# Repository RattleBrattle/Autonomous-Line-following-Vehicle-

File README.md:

## Autonomous Line Following Robot Vehicle

This project implements an autonomous line-following robot using an ATmega32A microcontroller. The robot is capable of detecting and following a line on the ground using TCRT5000 infrared sensors. It can move forward, turn left or right, and reverse based on the sensor inputs. Additionally, the robot is equipped with an HC-SR04 ultrasonic sensor for obstacle detection and an SG-90 servo motor to adjust the sensor's position for better obstacle avoidance.

### Features

- **Line Following**: Uses TCRT5000 infrared sensors to detect and follow a line.
- **Obstacle Detection**: Equipped with an HC-SR04 ultrasonic sensor to detect obstacles and avoid collisions.
- **Servo Motor Control**: Utilizes an SG-90 servo motor to adjust the position of the ultrasonic sensor for a broader range of detection.
- **Motor Control**: Controls DC motors using 2x L293D motor driver ICs for precise movement and direction control.
- **LCD Display**: Displays sensor readings, current direction, and status information (errors) on an LCD screen.

#### Project Flowchart
.png?raw=true)

- A higher detailed Flowchart PDF and image can be found in the "Project flow charts" file uploaded in the repository.

### Hardware Components

- ATmega32A Microcontroller
- TCRT5000 Infrared Sensors (3 units: left, center, right)
- HC-SR04 Ultrasonic Sensor
- SG-90 Servo Motor
- L293D Motor Driver ICs (2 units)
- DC Motors (4 units)
- LCD Display (16x2)
- Resistors, Capacitors, and other passive components

### Software Components

- **MCAL (Microcontroller Abstraction Layer)**
  - DIO (General Purpose Input/Output)
  - Timer (Timer0, Timer1)
  - ADC (Analog to Digital Converter)
  - USART (Universal Synchronous/Asynchronous Receiver/Transmitter)
  - Global Interrupt Enable (GIE)
  
- **HAL (Hardware Abstraction Layer)**
  - TCRT5000 Sensor Driver
  - HC-SR04 Ultrasonic Sensor Driver
  - SG-90 Servo Motor Driver
  - LCD Display Driver
 
### Proteus simulation circuit

  - **Simulation circuit**: In the folder uploaded to the repository named "Line-following robot", where I've created a circuit
  to simulate what the project would look like in real life as close as possible using libraries provided by syedzainnasir over [at this link!](https://www.theengineeringprojects.com/2021/05/infrared-tracker-sensor-library-for-proteus.html)

  - A higher quality image can be found inside the same folder mentioned above.

### Functionality

1. **Initialization**: 
   - Initializes GPIO pins, ADC, Timers, USART, and sensors.
   - Sets up the servo motor and ultrasonic sensor for obstacle detection.
   - Microcontroller controls the Motors and has 3 functions for them:
     1) Steer vehicle right by turning on the 2 right motors.
     2) Steer vehicle left by turning on the 2 left motors.
     3) Move vehicle forward by turning on all motors.
     4) Reverse vehicle backwards by reversing signals on all motors (not used in the project but the function is there and working).

2. **Line Following**:
   - Continuously reads the analog and digital values from the TCRT5000 sensors.
   - Adjusts the motor speeds and directions to follow the detected line.
   - Microcontroller constantly reads analog and digital values from the 3 TCRT sensors:
     1) If the left sensor digital value is 1 and the right sensor digital value is zero, then the vehicle turns left.
     2) If the right sensor digital value is 1 and the left sensor digital value is zero, then the vehicle turns right.
     3) If the middle sensor digital value is 0, the vehicle moves forward.

3. **Obstacle Detection and Avoidance**:
   - Uses the HC-SR04 sensor to measure distances to obstacles.
   - Adjusts the servo motor to scan the area.
   - When an obstacle is detected in range (<20CM), the MCU writes to LCD screen a warning and a Buzzer alarm sounds off.

4. **LCD Display**:
   - Displays the sensor readings and robot status on the LCD screen for monitoring. !!!(For debugging only)!!!
   - Displays current direction the vehicle is going, Obstacles detected when ultrasonic distance is <20CM, and errors when they occur. 

### Usage

1. **Hardware Setup**:
   - Connect the TCRT5000 sensors, HC-SR04 sensor, SG-90 servo motor, L293D motor driver ICs, and DC motors to the ATmega32A microcontroller as per the circuit diagram.

- A higher quality Schematic can be found inside the "PDF files" in the "KiCAD" schematic folder uploaded in the repository.
  
2. **Software Setup**:
   - Clone the repository and open the project in your preferred IDE (e.g., Atmel Studio Microchip).
   - Flash the firmware to the ATmega32A microcontroller (using Extreme Burner).

3. **Operation**:
   - Place the robot on a surface with a line to follow.
   - Power up the robot.
   - The robot will start following the line and avoid obstacles automatically.

### Files

- `main.c`: Main program file.
- `AUTOV_CONFIG.h`: Configuration file for the project.
- `AUTOV_INT.h`: Interface file with function prototypes and macros.
- `AUTOV_PROG.c`: Implementation file with the main logic for the autonomous vehicle functions.
- `TCRT_SENSOR.c`, `HCSR04_SENSOR.c`, `SERVO_MOTOR.c`: Driver files for the sensors and servo motor.

### Final project picture - FRONT

### Final project picture - TOP

### Final project picture - SIDE

### Contributing

Tell me your thoughts and ideas on how to make this project even better or faster.

You can contact me by email at: baselmohamed802@gmail.com.

Or message me on my LinkedIn! www.linkedin.com/in/basel-sayed-b11534243

### License

This project is licensed under the MIT License. See the [LICENSE](LICENSE) file for more details.

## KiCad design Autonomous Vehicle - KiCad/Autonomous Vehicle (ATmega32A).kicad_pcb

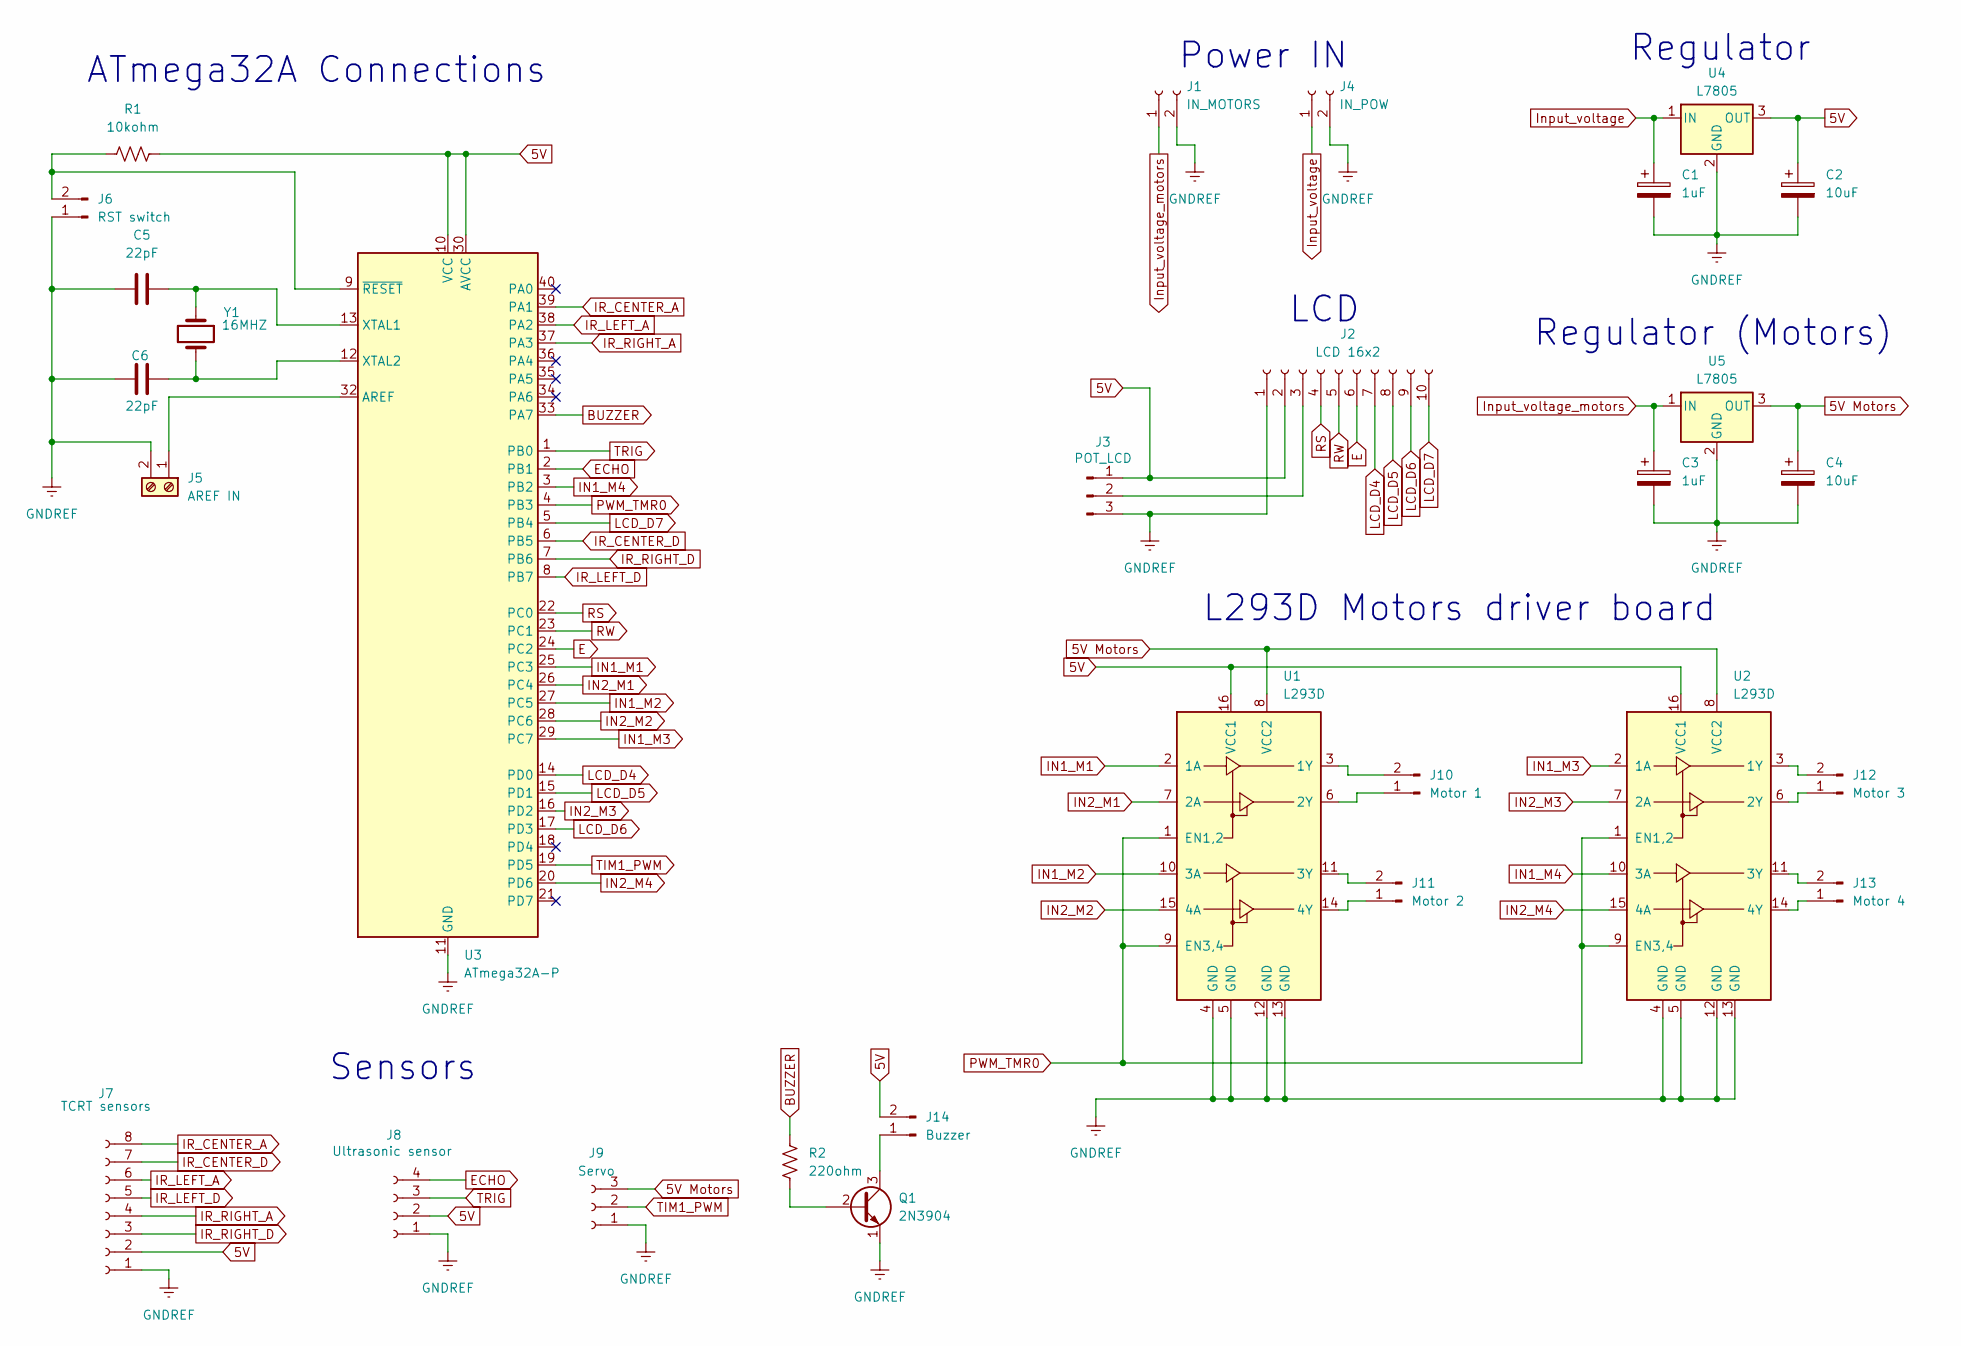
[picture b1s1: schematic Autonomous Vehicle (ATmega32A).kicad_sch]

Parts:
C1, C3: 1uF; CP_Radial_D5.0mm_P2.50mm
C2, C4: 10uF; CP_Radial_D5.0mm_P2.50mm
C5, C6: 22pF; C_Disc_D8.0mm_W2.5mm_P5.00mm
J1: IN_MOTORS; PinSocket_1x02_P2.54mm_Vertical
J2: LCD 16x2; PinSocket_1x10_P2.54mm_Vertical
J3: POT_LCD; PinHeader_1x03_P2.54mm_Vertical
J4: IN_POW; PinSocket_1x02_P2.54mm_Vertical
J5: AREF IN; TerminalBlock_Phoenix_MKDS-3-2-5.08_1x02_P5.08mm_Horizontal
J6: RST switch; PinHeader_1x02_P2.54mm_Vertical
J7: TCRT sensors; PinSocket_1x08_P2.54mm_Vertical
J8: Ultrasonic sensor; PinSocket_1x04_P2.54mm_Vertical
J9: Servo; PinSocket_1x03_P2.54mm_Vertical
J10: Motor 1; PinHeader_1x02_P2.54mm_Vertical
J11: Motor 2; PinHeader_1x02_P2.54mm_Vertical
J12: Motor 3; PinHeader_1x02_P2.54mm_Vertical
J13: Motor 4; PinHeader_1x02_P2.54mm_Vertical
J14: Buzzer; PinHeader_1x02_P2.54mm_Vertical
Q1: 2N3904; TO-92_Inline_Wide
R1: 10kohm; R_Axial_DIN0414_L11.9mm_D4.5mm_P7.62mm_Vertical
R2: 220ohm; R_Axial_DIN0414_L11.9mm_D4.5mm_P7.62mm_Vertical
U1, U2: L293D; DIP-16_W7.62mm
U3: ATmega32A-P; DIP-40_W15.24mm_Socket_LongPads
U4, U5: L7805; TO-220-3_Vertical
Y1: 16MHZ; Crystal_HC50_Vertical

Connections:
5V: C2.1, J2.2, J3.1, J7.2, J8.2, J14.2, R1.2, U1.16 (VCC1), U2.16 (VCC1), U3.10 (VCC), U3.30 (AVCC), U4.3 (OUT)
5V Motors: C4.1, J9.3, U1.8 (VCC2), U2.8 (VCC2), U5.3 (OUT)
BUZZER: R2.2, U3.33 (PA7)
E: J2.6, U3.24 (PC2)
ECHO: J8.4, U3.2 (PB1)
GNDREF: C1.2, C2.2, C3.2, C4.2, C5.1, C6.1, J1.2, J2.1, J3.3, J4.2, J5.2, J6.1, J7.1, J8.1, J9.1, Q1.1 (E), U1.4 (GND), U1.5 (GND), U1.12 (GND), U1.13 (GND), U2.4 (GND), U2.5 (GND), U2.12 (GND), U2.13 (GND), U3.11 (GND), U3.31 (GND), U4.2 (GND), U5.2 (GND)
IN1_M1: U1.2 (1A), U3.25 (PC3)
IN1_M2: U1.10 (3A), U3.27 (PC5)
IN1_M3: U2.2 (1A), U3.29 (PC7)
IN1_M4: U2.10 (3A), U3.3 (PB2)
IN2_M1: U1.7 (2A), U3.26 (PC4)
IN2_M2: U1.15 (4A), U3.28 (PC6)
IN2_M3: U2.7 (2A), U3.16 (PD2)
IN2_M4: U2.15 (4A), U3.20 (PD6)
IR_CENTER_A: J7.8, U3.39 (PA1)
IR_CENTER_D: J7.7, U3.6 (PB5)
IR_LEFT_A: J7.6, U3.38 (PA2)
IR_LEFT_D: J7.5, U3.8 (PB7)
IR_RIGHT_A: J7.4, U3.37 (PA3)
IR_RIGHT_D: J7.3, U3.7 (PB6)
Input_voltage: C1.1, J4.1, U4.1 (IN)
Input_voltage_motors: C3.1, J1.1, U5.1 (IN)
LCD_D4: J2.7, U3.14 (PD0)
LCD_D5: J2.8, U3.15 (PD1)
LCD_D6: J2.9, U3.17 (PD3)
LCD_D7: J2.10, U3.5 (PB4)
unnamed: J2.3, J3.2
unnamed: J5.1, U3.32 (AREF)
unnamed: J6.2, R1.1, U3.9 (~RESET)
unnamed: J10.1, U1.6 (2Y)
unnamed: J10.2, U1.3 (1Y)
unnamed: J11.1, U1.14 (4Y)
unnamed: J11.2, U1.11 (3Y)
unnamed: J12.1, U2.6 (2Y)
unnamed: J12.2, U2.3 (1Y)
unnamed: J13.1, U2.14 (4Y)
unnamed: J13.2, U2.11 (3Y)
unnamed: J14.1, Q1.3 (C)
unnamed: Q1.2 (B), R2.1
unnamed: C5.2, U3.13 (XTAL1), Y1.1
unnamed: C6.2, U3.12 (XTAL2), Y1.2
PWM_TMR0: U1.1 (EN1,2), U1.9 (EN3,4), U2.1 (EN1,2), U2.9 (EN3,4), U3.4 (PB3)
RS: J2.4, U3.22 (PC0)
RW: J2.5, U3.23 (PC1)
TIM1_PWM: J9.2, U3.19 (PD5)
TRIG: J8.3, U3.1 (PB0)

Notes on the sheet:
Regulator (Motors)
LCD
Power IN
Sensors
Regulator
ATmega32A Connections
L293D Motors driver board

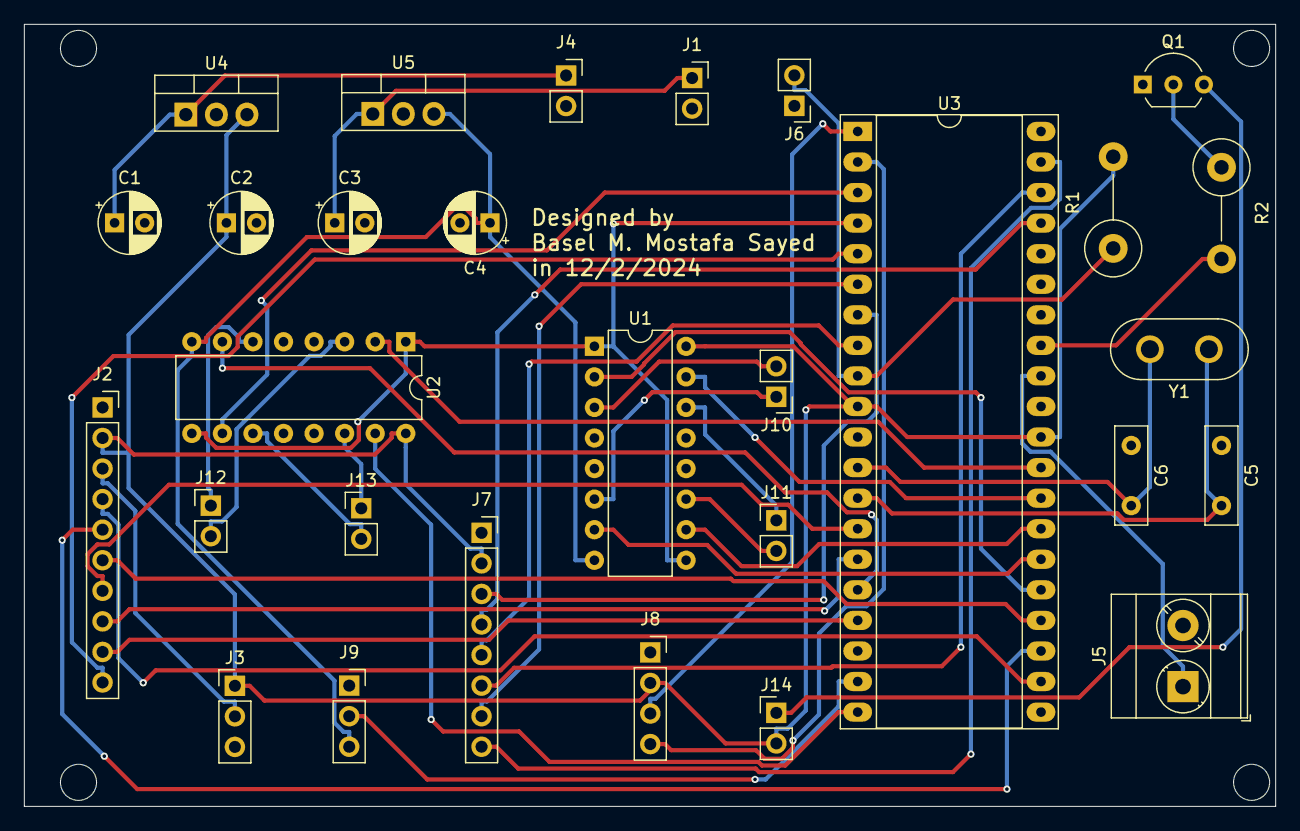
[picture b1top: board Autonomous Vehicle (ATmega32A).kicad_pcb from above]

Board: 2 copper layers, 104.0 x 65.0 mm, 29 parts (0 on the bottom side), 46 nets.

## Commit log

2024-11-30 Flowchart
    Adding flowchart and component images.
2024-11-30 KiCad schematic
2024-11-30 Proteus Simulation circuit
2024-11-30 Add Proteus schematic
2024-12-04 Update files
2024-12-04 Update presentation
2024-12-04 Upload Hex and debug files
2024-12-06 Update 1
2024-12-06 Add Project code
2024-12-06 Remove personal code
2024-12-06 Remove Uneccessary
2024-12-06 Change name of folder
2024-12-07 Upload Final Project pictures
2024-12-11 Update Project code
2024-12-11 Remove unneccessary
2024-12-28 FIN UP1
